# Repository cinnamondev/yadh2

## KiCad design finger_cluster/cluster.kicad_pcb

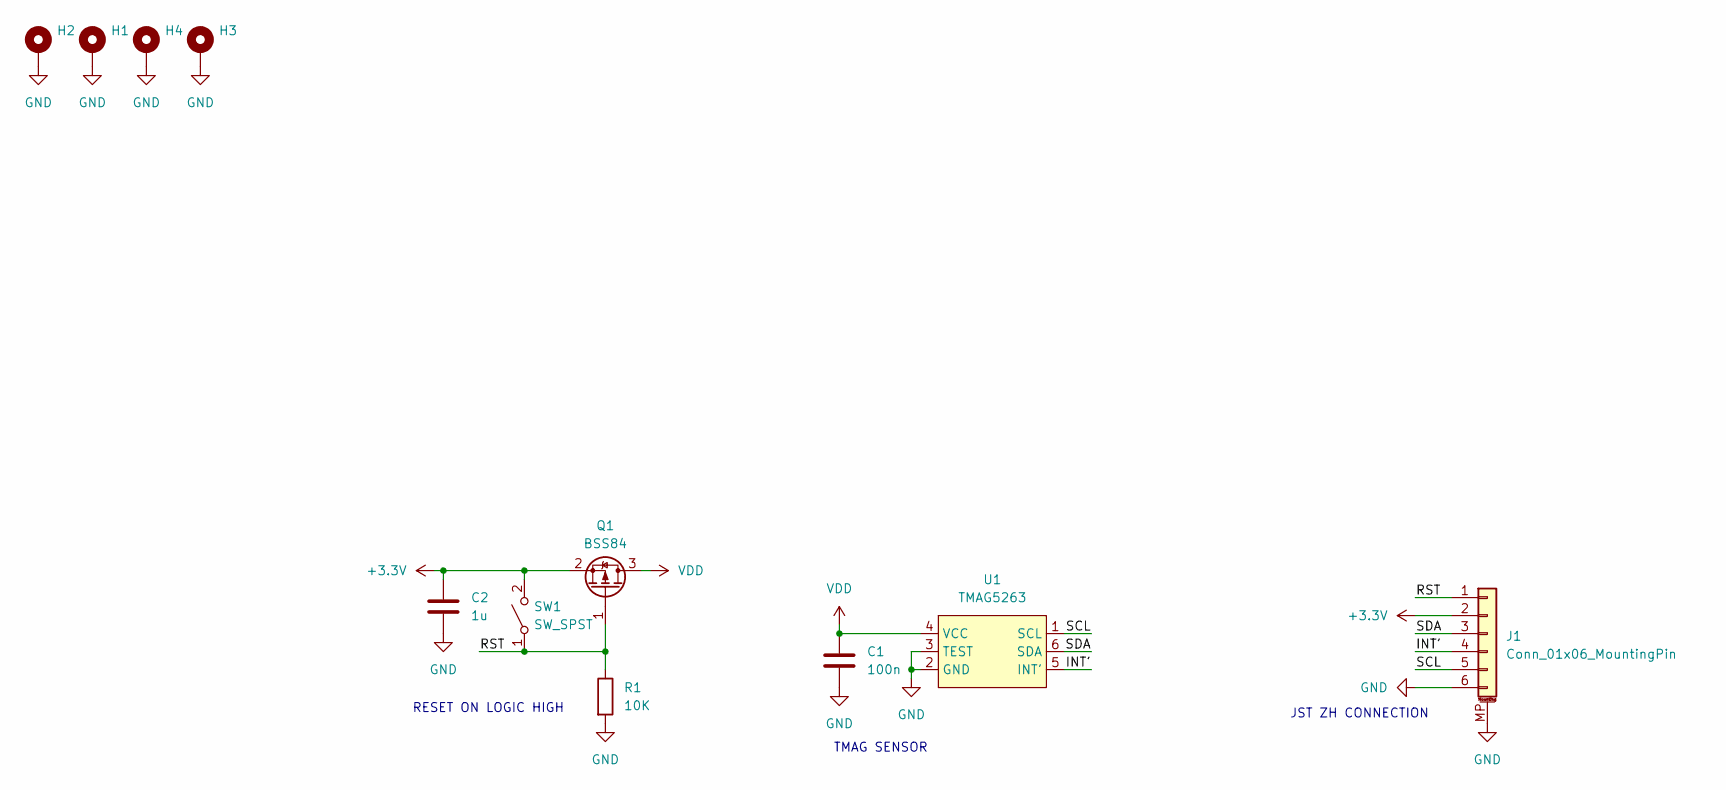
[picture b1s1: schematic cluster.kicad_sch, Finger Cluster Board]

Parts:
C1: 100n; C_0805_2012Metric_Pad1.18x1.45mm_HandSolder
C2: 1u; C_0805_2012Metric_Pad1.18x1.45mm_HandSolder
H1, H2, H3, H4: MountingHole_Pad; MountingHole_2.7mm_M2.5_DIN965_Pad
J1: Conn_01x06_MountingPin; JST_ZH_S6B-ZR-SM4A-TF_1x06-1MP_P1.50mm_Horizontal
Q1: BSS84; SOT-23
R1: 10K; R_0805_2012Metric_Pad1.20x1.40mm_HandSolder
SW1: SW_SPST; SW_Push_SPST_NO_Alps_SKRK
U1: TMAG5263; SOT-23-6_Handsoldering

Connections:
+3.3V: C2.1, J1.2, Q1.2 (S), SW1.2 (B)
/INT': J1.4, U1.5 (INT')
/RST: J1.1, Q1.1 (G), R1.1, SW1.1 (A)
/SCL: J1.5, U1.1 (SCL)
/SDA: J1.3, U1.6 (SDA)
GND: C1.2, C2.2, H1.1, H2.1, H3.1, H4.1, J1.6, J1.MP (MountPin), R1.2, U1.2 (GND), U1.3 (TEST); also elsewhere on the board
VDD: C1.1, Q1.3 (D), U1.4 (VCC)

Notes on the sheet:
RESET ON LOGIC HIGH
TMAG SENSOR
JST ZH CONNECTION

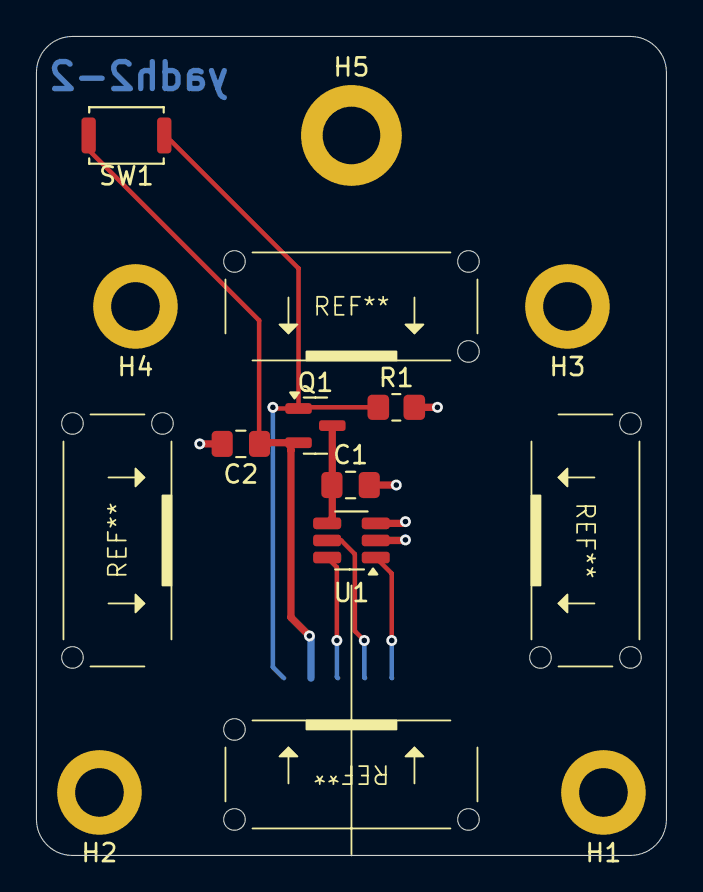
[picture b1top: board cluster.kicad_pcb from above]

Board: 2 copper layers, 35.0 x 45.5 mm, 12 parts (1 on the bottom side), 7 nets.

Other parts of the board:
H5: MountingHole_Pad; MountingHole_3.2mm_M3_DIN965_Pad

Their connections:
GND: H5.1; also elsewhere on the board

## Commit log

2025-04-19 v2 basic playing around, basic cluser pcb. need to work on cluster design etc and keys from base directional key designs (puleld from v1)
2025-04-22 cluster key resizes
2025-04-23 cluster aluminium basic
2025-04-24 cleaned up cluster model, folder structure
2025-04-25 cluster prog
2026-01-20 finger cluster 2 testing + some old wip things, trying to start work on this proper again
2026-01-23 finger cluster. need to update south key
